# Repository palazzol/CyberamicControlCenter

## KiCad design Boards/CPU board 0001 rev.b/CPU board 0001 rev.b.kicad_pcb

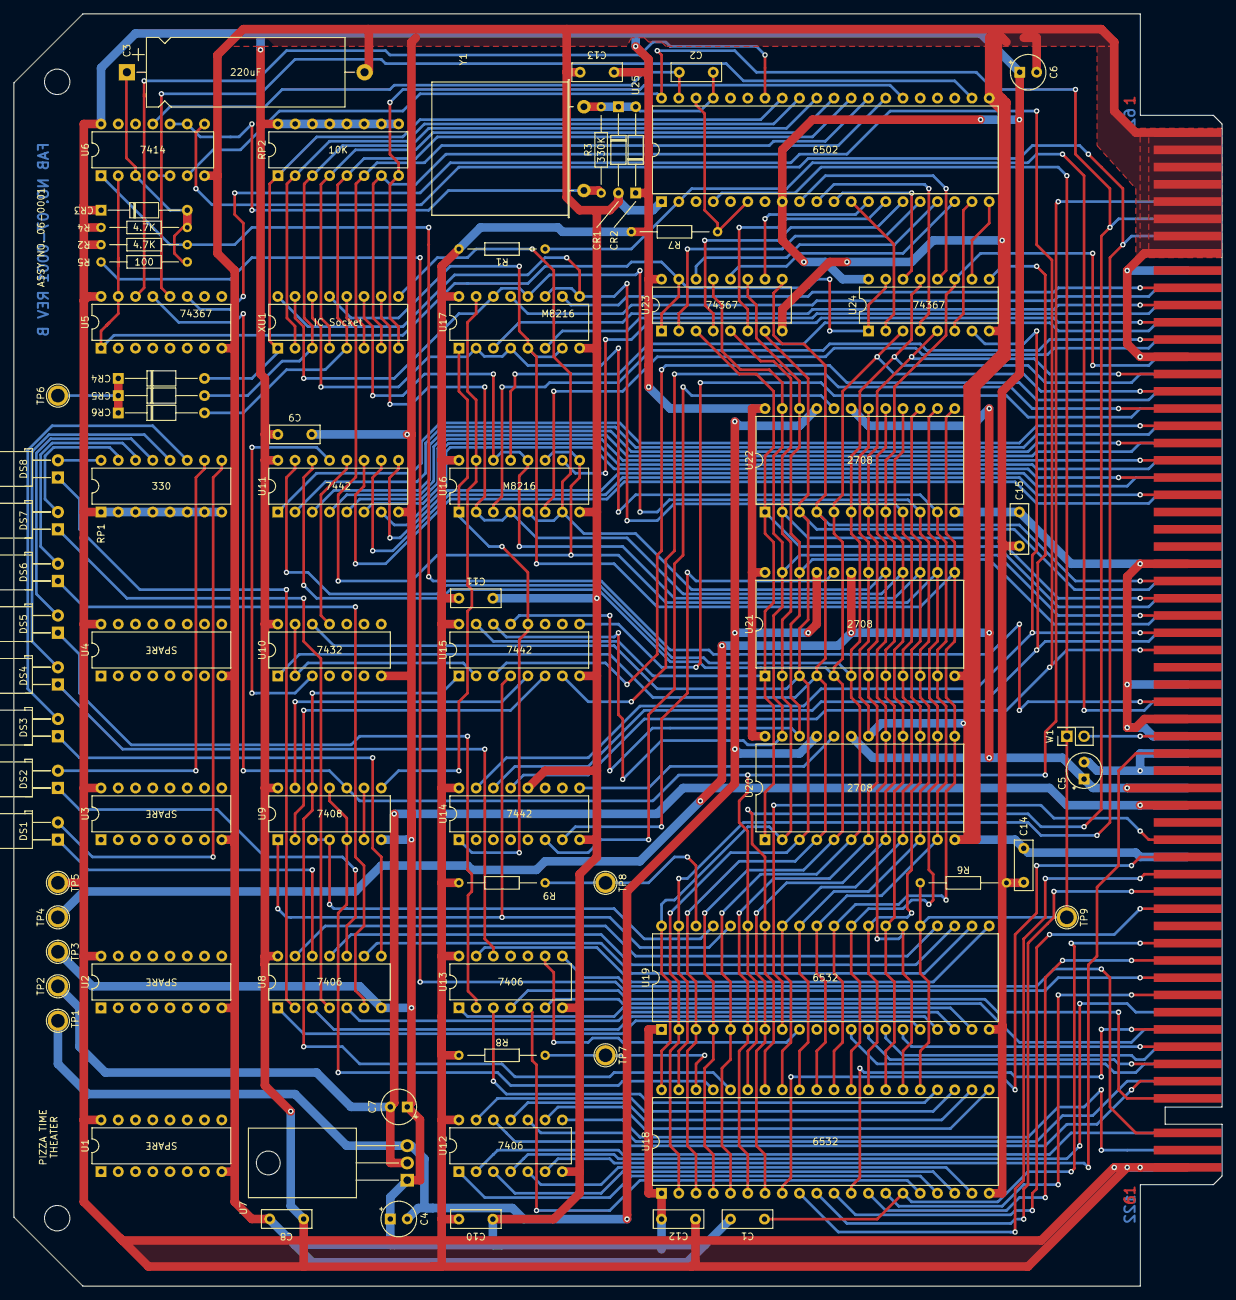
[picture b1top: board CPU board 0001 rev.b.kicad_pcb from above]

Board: 2 copper layers, 177.9 x 187.4 mm, 78 parts (0 on the bottom side), 157 nets.

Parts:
C1, C8, C9, C10, C11, C12, C13, C14, C15: 100nF; C_Rect_L7.2mm_W2.5mm_P5.00mm_FKS2_FKP2_MKS2_MKP2
C2: 10pF; C_Rect_L7.2mm_W2.5mm_P5.00mm_FKS2_FKP2_MKS2_MKP2
C3: 220uF; CP_Axial_L29.0mm_D10.0mm_P35.00mm_Horizontal
C4, C5, C6, C7: 4.7uF; CP_Radial_Tantal_D5.0mm_P2.50mm
CR1, CR2, CR3, CR4, CR5, CR6: 1N914; D_DO-35_SOD27_P12.70mm_Horizontal
DS1, DS2, DS3, DS4, DS5, DS6, DS7, DS8: LED; LED_D5.0mm_Horizontal_O3.81mm_Z15.0mm reversed
J1: CEC card edge connector large; Chuck_E_Cheese_large_card_edge
R1, R2, R4, R6, R7, R8, R9: 4.7K; R_Axial_DIN0204_L3.6mm_D1.6mm_P12.7mm_Horizontal
R3: 330K; R_Axial_DIN0204_L3.6mm_D1.6mm_P12.7mm_Horizontal
R5: 100; R_Axial_DIN0204_L3.6mm_D1.6mm_P12.7mm_Horizontal
RP1: 330; DIP-16_W7.62mm
RP2: 10K; DIP-16_W7.62mm
TP1: -5v; TestPoint_Plated_Hole_D2.0mm
TP2: -12v; TestPoint_Plated_Hole_D2.0mm
TP3: GND; TestPoint_Plated_Hole_D2.0mm
TP4: +12v; TestPoint_Plated_Hole_D2.0mm
TP5: +5v; TestPoint_Plated_Hole_D2.0mm
TP6: ~{0/2/4}; TestPoint_Plated_Hole_D2.0mm
TP7: U18 CS; TestPoint_Plated_Hole_D2.0mm
TP8: U19 CS; TestPoint_Plated_Hole_D2.0mm
TP9: IRQ; TestPoint_Plated_Hole_D2.0mm
U1, U2, U3, U4: SPARE; DIP-16_W7.62mm
U5, U23, U24: 74367; DIP-16_W7.62mm
U6: 7414; DIP-14_W7.62mm
U7: LM7905_TO220; TO-220-3_Horizontal_TabDown
U8, U12, U13: 7406; DIP-14_W7.62mm
U9: 7408; DIP-14_W7.62mm
U10: 7432; DIP-14_W7.62mm
U11, U14, U15: 7442; DIP-16_W7.62mm
U16, U17: M8216; DIP-16_W7.62mm
U18, U19: 6532; DIP-40_W15.24mm
U20, U21, U22: 2708; DIP-24_W15.24mm
U25: 6502; DIP-40_W15.24mm
W1: IRQ; PinSocket_2x01_P2.54mm_Vertical
XU1: IC Socket; DIP-16_W7.62mm
Y1: 1Mhz; Crystal_HC33-U_Horizontal

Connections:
+5V: C6.1, C8.1, C9.1, C10.1, C11.1, C12.1, C13.1, C14.1, C15.1, CR2.1 (K), CR3.1 (K), J1.61, J1.122, R1.1, R2.1, R4.1, R6.1, R7.1, R8.1, R9.1, RP1.1 (R1.1), RP1.2 (R2.1), RP1.3 (R3.1), RP1.4 (R4.1), RP1.5 (R5.1), RP1.6 (R6.1), RP1.7 (R7.1), RP1.8 (R8.1), RP2.9 (R8.2), RP2.10 (R7.2), RP2.11 (R6.2), RP2.12 (R5.2), RP2.13 (R4.2), RP2.14 (R3.2), RP2.15 (R2.2), RP2.16 (R1.2), TP5.1, U1.16 (R1.2), U2.16 (R1.2), U3.16 (R1.2), U4.16 (R1.2), U5.16 (VCC), U6.14 (VCC), U8.14 (VCC), U9.14 (VCC), U10.14 (VCC), U11.16 (VCC), U12.14 (VCC), U13.14 (VCC), U14.16 (VCC), U15.16 (VCC), U16.16 (VCC), U17.16 (VCC), U18.20 (Vcc), U19.20 (Vcc), U20.24 (VCC), U21.24 (VCC), U22.24 (VCC), U23.16 (VCC), U24.16 (VCC), U25.8 (Vcc)
+12V: C5.1, J1.39, J1.100, TP4.1, U20.19 (VDD), U21.19 (VDD), U22.19 (VDD)
-5V: C4.2, TP1.1, U7.3 (VO), U20.21 (VBB), U21.21 (VBB), U22.21 (VBB)
-12V: C7.2, J1.40, J1.101, TP2.1, U7.2 (VI)
A0: U24.12 (I5), U25.9 (A0)
A1: U24.4 (I2), U25.10 (A1)
A2: U24.14 (I6), U25.11 (A2)
A3: U24.2 (I1), U25.12 (A3)
A4: U23.10 (I4), U25.13 (A4)
A5: U23.6 (I3), U25.14 (A5)
A6: U23.4 (I2), U25.15 (A6)
A7: U23.2 (I1), U25.16 (A7)
A8: U23.14 (I6), U25.17 (A8)
A9: U23.12 (I5), U25.18 (A9)
A10: U24.6 (I3), U25.19 (A10)
A11: U24.10 (I4), U25.20 (A11)
A12: U5.12 (I5), U25.22 (A12)
AGC 1: J1.116, U19.12 (PA4)
AGC 2: J1.55, U19.13 (PA5)
AGC 4: J1.115, U19.14 (PA6)
AGC 8: J1.54, U19.15 (PA7)
AUDIO: J1.78, U15.9 (7)
B'DAY in: J1.44, U18.9 (PA1)
B'DAY out: J1.56, U12.12
BA0: J1.75, U18.7 (A0), U19.7 (A0), U20.8 (A0), U21.8 (A0), U22.8 (A0), U24.11 (O5b)
BA1: J1.15, U18.6 (A1), U19.6 (A1), U20.7 (A1), U21.7 (A1), U22.7 (A1), U24.5 (O2a)
BA2: J1.76, U11.15 (A0), U18.5 (A2), U19.5 (A2), U20.6 (A2), U21.6 (A2), U22.6 (A2), U24.13 (O6b)
BA3: J1.16, U11.14 (A1), U18.4 (A3), U19.4 (A3), U20.5 (A3), U21.5 (A3), U22.5 (A3), U24.3 (O1a)
BA4: J1.27, U10.1, U18.3 (A4), U19.3 (A4), U20.4 (A4), U21.4 (A4), U22.4 (A4), U23.9 (O4a)
BA5: J1.88, U10.12, U18.2 (A5), U19.2 (A5), U20.3 (A5), U21.3 (A5), U22.3 (A5), U23.7 (O3a)
BA6: J1.28, U18.40 (A6), U19.40 (A6), U20.2 (A6), U21.2 (A6), U22.2 (A6), U23.5 (O2a)
BA7: J1.89, U15.15 (A0), U20.1 (A7), U21.1 (A7), U22.1 (A7), U23.3 (O1a)
BA8: J1.29, U15.14 (A1), U20.23 (A8), U21.23 (A8), U22.23 (A8), U23.13 (O6b)
BA9: J1.90, U15.13 (A2), U20.22 (A9), U21.22 (A9), U22.22 (A9), U23.11 (O5b)
BA10: J1.30, U14.15 (A0), U24.7 (O3a)
BA11: J1.91, U14.14 (A1), U24.9 (O4a)
BA12: J1.31, U5.11 (O5b), U14.13 (A2)
BS1: J1.18, U11.1 (0)
BS2: J1.79, U11.2 (1)
BS3: J1.19, U11.3 (2)
BS4: J1.80, U11.4 (3)
BS5: J1.20, U11.5 (4)
BS6: J1.81, U11.6 (5)
BS7: J1.21, U11.7 (6)
BS8: J1.82, U11.9 (7)
BS9: J1.22, U11.10 (8)
BS10: J1.83, U11.11 (9)
CHEER in: J1.43, U18.8 (PA0)
CHEER out: J1.57, U13.4
D0: U17.9 (DI2), U17.11 (DO2), U18.33 (D0), U19.33 (D0), U20.9 (D0), U21.9 (D0), U22.9 (D0), XU1.16 (R1.2)
D1: U17.12 (DI3), U17.14 (DO3), U18.32 (D1), U19.32 (D1), U20.10 (D1), U21.10 (D1), U22.10 (D1), XU1.15 (R2.2)
D2: U17.2 (DO0), U17.4 (DI0), U18.31 (D2), U19.31 (D2), U20.11 (D2), U21.11 (D2), U22.11 (D2), XU1.14 (R3.2)
D3: U17.5 (DO1), U17.7 (DI1), U18.30 (D3), U19.30 (D3), U20.13 (D3), U21.13 (D3), U22.13 (D3), XU1.13 (R4.2)
D4: U16.9 (DI2), U16.11 (DO2), U18.29 (D4), U19.29 (D4), U20.14 (D4), U21.14 (D4), U22.14 (D4), XU1.12 (R5.2)
D5: U16.12 (DI3), U16.14 (DO3), U18.28 (D5), U19.28 (D5), U20.15 (D5), U21.15 (D5), U22.15 (D5), XU1.11 (R6.2)
D6: U16.2 (DO0), U16.4 (DI0), U18.27 (D6), U19.27 (D6), U20.16 (D6), U21.16 (D6), U22.16 (D6), XU1.10 (R7.2)
D7: U16.5 (DO1), U16.7 (DI1), U18.26 (D7), U19.26 (D7), U20.17 (D7), U21.17 (D7), U22.17 (D7), XU1.9 (R8.2)
DB0: J1.10, U17.10 (DB2)
DB1: J1.71, U17.13 (DB3)
DB2: J1.11, U17.3 (DB0)
DB3: J1.72, U17.6 (DB1)
DB4: J1.12, U16.10 (DB2)
DB5: J1.73, U16.13 (DB3)
DB6: J1.13, U16.3 (DB0)
DB7: J1.74, U16.6 (DB1)
DIAG in: J1.53, U18.12 (PA4)
DIAG out: J1.37, U12.6
GND: C1.2, C3.2, C4.1, C5.2, C6.2, C7.1, C8.2, C9.2, C10.2, C11.2, C12.2, C13.2, C14.2, C15.2, CR1.2 (A), J1.1, J1.2, J1.3, J1.4, J1.5, J1.6, J1.7, J1.8, J1.14, J1.26, J1.35, J1.70, J1.94, J1.97, J1.98, J1.99, J1.103, J1.104, J1.105, J1.106, J1.107, J1.108, J1.109, J1.110, J1.111, TP3.1, U1.8 (R8.1), U2.8 (R8.1), U3.8 (R8.1), U4.8 (R8.1), U5.8 (GND), U6.7 (GND), U7.1 (GND), U8.7 (GND), U9.7 (GND), U10.7 (GND), U11.8 (GND), U12.7 (GND), U13.7 (GND), U14.8 (GND), U14.12 (A3), U15.8 (GND), U16.8 (GND), U17.8 (GND), U18.1 (GND), U19.1 (GND), U20.12 (GND), U20.18 (PGM), U21.12 (GND), U21.18 (PGM), U22.12 (GND), U22.18 (PGM), U23.8 (GND), U24.8 (GND), U25.1 (VSS), U25.21 (GND)
INTRO in: J1.45, U18.10 (PA2)
INTRO out: J1.117, U12.10
MIKE SW.: J1.42, U19.8 (PA0)
NEXT in: J1.49, U18.13 (PA5)
NEXT out: J1.113, U12.4
unnamed: C2.1, CR1.1 (K), CR2.2 (A), R3.2, U25.37 (00), Y1.1
unnamed: C3.1, CR3.2 (A), R4.2, R5.2, U6.3
unnamed: CR4.2 (A), RP2.1 (R1.1), U25.33 (D0), XU1.1 (R1.1)
unnamed: CR4.1 (K), CR5.1 (K), CR6.1 (K), TP6.1
unnamed: CR5.2 (A), RP2.3 (R3.1), U25.31 (D2), XU1.3 (R3.1)
unnamed: CR6.2 (A), RP2.5 (R5.1), U25.29 (D4), XU1.5 (R5.1)
unnamed: DS1.2 (A), RP1.9 (R8.2)
unnamed: DS1.1 (K), U8.12
unnamed: DS2.2 (A), RP1.10 (R7.2)
unnamed: DS2.1 (K), U8.10
unnamed: DS3.2 (A), RP1.11 (R6.2)
unnamed: DS3.1 (K), U8.8
unnamed: DS4.2 (A), RP1.12 (R5.2)
unnamed: DS4.1 (K), U13.12
unnamed: DS5.2 (A), RP1.13 (R4.2)
unnamed: DS5.1 (K), U13.2
unnamed: DS6.2 (A), RP1.14 (R3.2)
unnamed: DS6.1 (K), U8.6
unnamed: DS7.2 (A), RP1.15 (R2.2)
unnamed: DS7.1 (K), U8.4
unnamed: DS8.2 (A), RP1.16 (R1.2)
unnamed: DS8.1 (K), U8.2
unnamed: R3.1, U6.9, U6.10, Y1.2
unnamed: RP2.2 (R2.1), U25.32 (D1), XU1.2 (R2.1)
unnamed: RP2.4 (R4.1), U25.30 (D3), XU1.4 (R4.1)
unnamed: RP2.6 (R6.1), U25.28 (D5), XU1.6 (R6.1)
unnamed: RP2.7 (R7.1), U25.27 (D6), XU1.7 (R7.1)
unnamed: RP2.8 (R8.1), U25.26 (D7), XU1.8 (R8.1)
unnamed: U6.4, U6.5
unnamed: U9.6, U9.9
unnamed: U10.3, U11.13 (A2)
unnamed: U10.11, U11.12 (A3)
unnamed: U14.1 (0), U15.12 (A3), U16.1 (~CS), U17.1 (~CS)
unnamed: U9.8, U16.15 (IN/~OUT), U17.15 (IN/~OUT)
unnamed: R8.2, TP7.1, U18.38 (CS1)
unnamed: U13.3, U18.24 (PB0)
unnamed: U12.13, U18.23 (PB1)
unnamed: U12.11, U18.22 (PB2)
unnamed: U12.9, U18.21 (PB3)
unnamed: U12.5, U18.19 (PB4)
unnamed: U12.3, U18.18 (PB5)
unnamed: U12.1, U18.17 (PB6)
unnamed: U13.5, U18.16 (PB7)
unnamed: U9.5, U9.11, U18.37 (~CS2)
unnamed: R9.2, TP8.1, U19.38 (CS1)
unnamed: U13.9, U19.9 (PA1)
unnamed: U8.13, U19.24 (PB0)
unnamed: U8.11, U19.23 (PB1)
unnamed: U8.9, U19.22 (PB2)
unnamed: U13.13, U19.21 (PB3)
unnamed: U13.1, U19.19 (PB4)
unnamed: U8.5, U19.18 (PB5)
unnamed: U8.3, U19.17 (PB6)
unnamed: U8.1, U19.16 (PB7)
unnamed: U9.3, U9.4, U19.37 (~CS2)
unnamed: U5.1 (OEa), U5.15 (OEb), U6.2, U23.1 (OEa), U23.15 (OEb), U24.1 (OEa), U24.15 (OEb)
unnamed: C2.2, U6.11, U25.39 (02)
unnamed: R7.2, U25.6 (~NMI), U25.38 (SO)
PHI2: J1.68, U6.8, U18.39 (02), U19.39 (02)
PROG in: C1.1, J1.48, U18.15 (PA7)
PROG out: J1.114, U13.6
RDY: J1.95, R1.2, U25.2 (RDY)
RESET out: J1.59, U13.8
R/~W: J1.66, U5.13 (O6b), U9.10, U18.35 (R/~W), U19.35 (R/~W)
SKIP in: J1.51, U18.14 (PA6)
SKIP out: J1.120, U12.2
SPEC in: J1.46, U18.11 (PA3)
SPEC out: J1.121, U12.8
UART: J1.77, U15.3 (2)
XPRT: J1.17, U15.7 (6)
cpu R/~W: U5.14 (I6), U25.34 (R/~W)
/CARDS: U10.2, U10.13, U15.2 (1)
/CS U20: U14.9 (7), U20.20 (~CS)
/CS U21: U14.7 (6), U21.20 (~CS)
/CS U22: U14.6 (5), U22.20 (~CS)
/HOLD in: J1.34, R2.2, U6.1
/IRQ: R6.2, TP9.1, U18.25 (~IRQ), U19.25 (~IRQ), U25.4 (~IRQ), W1.1
/IRQ out: J1.36, W1.2
/RAM: U9.12, U15.1 (0), U18.36 (/RS)
/RESET: J1.67, U6.6, U18.34 (~RESET), U19.34 (~RESET), U25.40 (~RESET)
/RESET in: J1.50, R5.1
/STACK: U9.1, U15.4 (3), U19.36 (/RS)
/U18: U9.13, U15.5 (4)
/U19: U9.2, U15.6 (5)

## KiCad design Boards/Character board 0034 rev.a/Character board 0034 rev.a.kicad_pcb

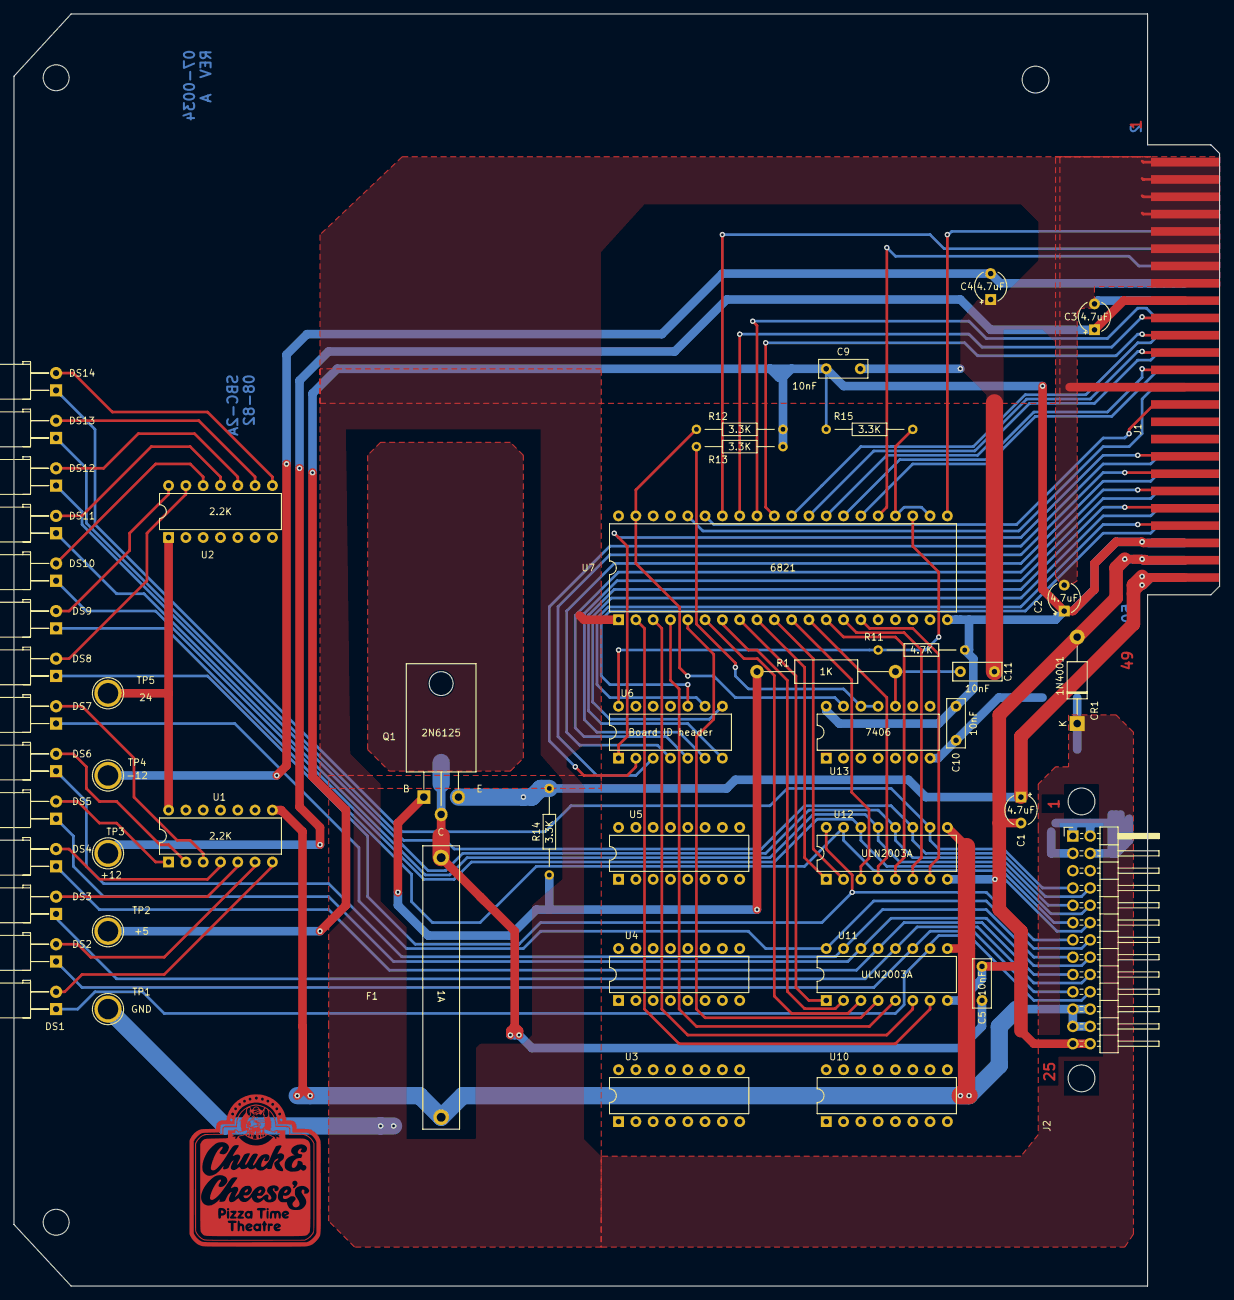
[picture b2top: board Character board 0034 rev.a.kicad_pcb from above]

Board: 2 copper layers, 176.9 x 186.7 mm, 49 parts (0 on the bottom side), 79 nets.

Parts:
C1, C2, C3, C4: 4.7uF; CP_Radial_Tantal_D4mm_P3.81mm
C5, C9, C10, C11: 10nF; C_Rect_L7.0mm_W2.5mm_P5.00mm
CR1: 1N4001; D_DO-41_SOD81_P12.70mm_Horizontal
DS1, DS2, DS3, DS4, DS5, DS6, DS7, DS8, DS9, DS10, DS11, DS12, DS13, DS14: LED; LED_D5.0mm_Horizontal_O3.81mm_Z15.0mm reversed
F1: 1A; Fuseholder_Littelfuse_445_030_series_5x30mm
J1: card edge; Chuck_E_Cheese_small_card_edge
J2: character connector; PinHeader_2x13_P2.54mm_Horizontal
Q1: 2N6125; TO-220-3_Horizontal_TabDown
R1: 1K; R_Axial_DIN0309_L9.0mm_D3.2mm_P20.32mm_Horizontal
R11: 4.7K; R_Axial_DIN0204_L3.6mm_D1.6mm_P12.7mm_Horizontal
R12, R13, R14, R15: 3.3K; R_Axial_DIN0204_L3.6mm_D1.6mm_P12.7mm_Horizontal
TP1: GND; TestPoint_Plated_Hole_D3.0mm
TP2: +5; TestPoint_Plated_Hole_D3.0mm
TP3: +12; TestPoint_Plated_Hole_D3.0mm
TP4: -12; TestPoint_Plated_Hole_D3.0mm
TP5: 24; TestPoint_Plated_Hole_D3.0mm
U1, U2: 2.2K; DIP-14_W7.62mm
U3, U4, U5, U10: Unused DIP; DIP-16_W7.62mm
U6: Board ID header; DIP-14_W7.62mm
U7: 6821; DIP-40_W15.24mm
U11, U12: ULN2003A; DIP-16_W7.62mm
U13: 7406; DIP-14_W7.62mm

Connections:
5V: C2.1, C9.1, C10.1, J1.45, J1.46, R11.1, R12.2, R13.2, R15.1, TP2.1, U7.20 (VCC), U13.14 (VCC)
12V: C3.1, J1.17, TP3.1
24R: C1.2, C5.1, CR1.2 (A), J1.47, J1.48, J2.25, J2.26, U11.8 (GND), U12.8 (GND)
24V: C1.1, J1.49, J1.50, Q1.3 (E), R14.2
24Vout: F1.2, J2.21, J2.22, J2.23, J2.24, TP5.1, U1.8 (R7.2), U1.9 (R6.2), U1.10 (R5.2), U1.11 (R4.2), U1.12 (R3.2), U1.13 (R2.2), U1.14 (R1.2), U2.1 (R1.1), U2.2 (R2.1), U2.3 (R3.1), U2.4 (R4.1), U2.5 (R5.1), U2.6 (R6.1), U2.7 (R7.1), U11.9 (COM), U12.9 (COM)
-12V: C4.2, J1.16, TP4.1
A0out: DS1.1 (K), J2.20, U11.10 (O7)
A1out: DS2.1 (K), J2.19, U11.11 (O6)
A2out: DS3.1 (K), J2.18, U11.12 (O5)
A3out: DS4.1 (K), J2.17, U11.13 (O4)
A4out: DS5.1 (K), J2.16, U11.14 (O3)
A5out: DS6.1 (K), J2.15, U11.15 (O2)
A6out: DS7.1 (K), J2.14, U11.16 (O1)
A7out: DS8.1 (K), J2.13, U12.16 (O1)
B0out: DS9.1 (K), J2.12, U12.15 (O2)
B1out: DS10.1 (K), J2.11, U12.14 (O3)
B2out: DS11.1 (K), J2.10, U12.13 (O4)
B3out: DS12.1 (K), J2.9, U12.12 (O5)
B4out: DS13.1 (K), J2.8, U12.11 (O6)
B5out: DS14.1 (K), J2.7, U12.10 (O7)
BA0: J1.28, U7.36 (RS0)
BA1: J1.29, U7.35 (RS1)
BS1: J1.35, U6.1
BS2: J1.36, U6.2
BS3: J1.37, U6.3
BS4: J1.38, U6.4
BS5: J1.39, U6.5
BS6: J1.40, U6.6
BS7: J1.41, U6.7
BS8: J1.42, U6.8
BS9: J1.43, U6.9
BS10: J1.44, U6.10
DBB0: J1.19, U7.33 (D0)
DBB1: J1.20, U7.32 (D1)
DBB2: J1.21, U7.31 (D2)
DBB3: J1.22, U7.30 (D3)
DBB4: J1.23, U7.29 (D4)
DBB5: J1.24, U7.28 (D5)
DBB6: J1.25, U7.27 (D6)
DBB7: J1.26, U7.26 (D7)
GND: C2.2, C3.2, C4.1, C9.2, C10.2, C11.2, CR1.1 (K), J1.1, J1.3, J1.5, J1.7, J1.9, J1.11, J1.13, J1.15, J1.18, J1.27, J2.1, J2.2, J2.3, J2.4, TP1.1, U7.1 (VSS), U13.7 (GND)
unnamed: C11.1, R1.2, U13.10
unnamed: DS1.2 (A), U1.7 (R7.1)
unnamed: DS2.2 (A), U1.6 (R6.1)
unnamed: DS3.2 (A), U1.5 (R5.1)
unnamed: DS4.2 (A), U1.4 (R4.1)
unnamed: DS5.2 (A), U1.1 (R1.1)
unnamed: DS6.2 (A), U1.2 (R2.1)
unnamed: DS7.2 (A), U1.3 (R3.1)
unnamed: DS8.2 (A), U2.13 (R2.2)
unnamed: DS9.2 (A), U2.14 (R1.2)
unnamed: DS10.2 (A), U2.12 (R3.2)
unnamed: DS11.2 (A), U2.11 (R4.2)
unnamed: DS12.2 (A), U2.10 (R5.2)
unnamed: DS13.2 (A), U2.9 (R6.2)
unnamed: DS14.2 (A), U2.8 (R7.2)
unnamed: Q1.1 (B), R1.1, R14.1
unnamed: C5.2, F1.1, Q1.2 (C)
unnamed: R13.1, U13.11, U13.12
unnamed: R11.2, U6.14, U7.23 (~CS2)
unnamed: R12.1, U7.39 (CA2), U13.13
unnamed: R15.2, U7.22 (CS0), U7.24 (CS1)
PA0: U7.2 (PA0), U11.7 (I7)
PA1: U7.3 (PA1), U11.6 (I6)
PA2: U7.4 (PA2), U11.5 (I5)
PA3: U7.5 (PA3), U11.4 (I4)
PA4: U7.6 (PA4), U11.3 (I3)
PA5: U7.7 (PA5), U11.2 (I2)
PA6: U7.8 (PA6), U11.1 (I1)
PA7: U7.9 (PA7), U12.1 (I1)
PB0: U7.10 (PB0), U12.2 (I2)
PB1: U7.11 (PB1), U12.3 (I3)
PB2: U7.12 (PB2), U12.4 (I4)
PB3: U7.13 (PB3), U12.5 (I5)
PB4: U7.14 (PB4), U12.6 (I6)
PB5: U7.15 (PB5), U12.7 (I7)
PHI2: J1.14, U7.25 (ENABLE)
R/~W: J1.10, U7.21 (R/~W)
~MRST: J1.12, U7.34 (~RESET)

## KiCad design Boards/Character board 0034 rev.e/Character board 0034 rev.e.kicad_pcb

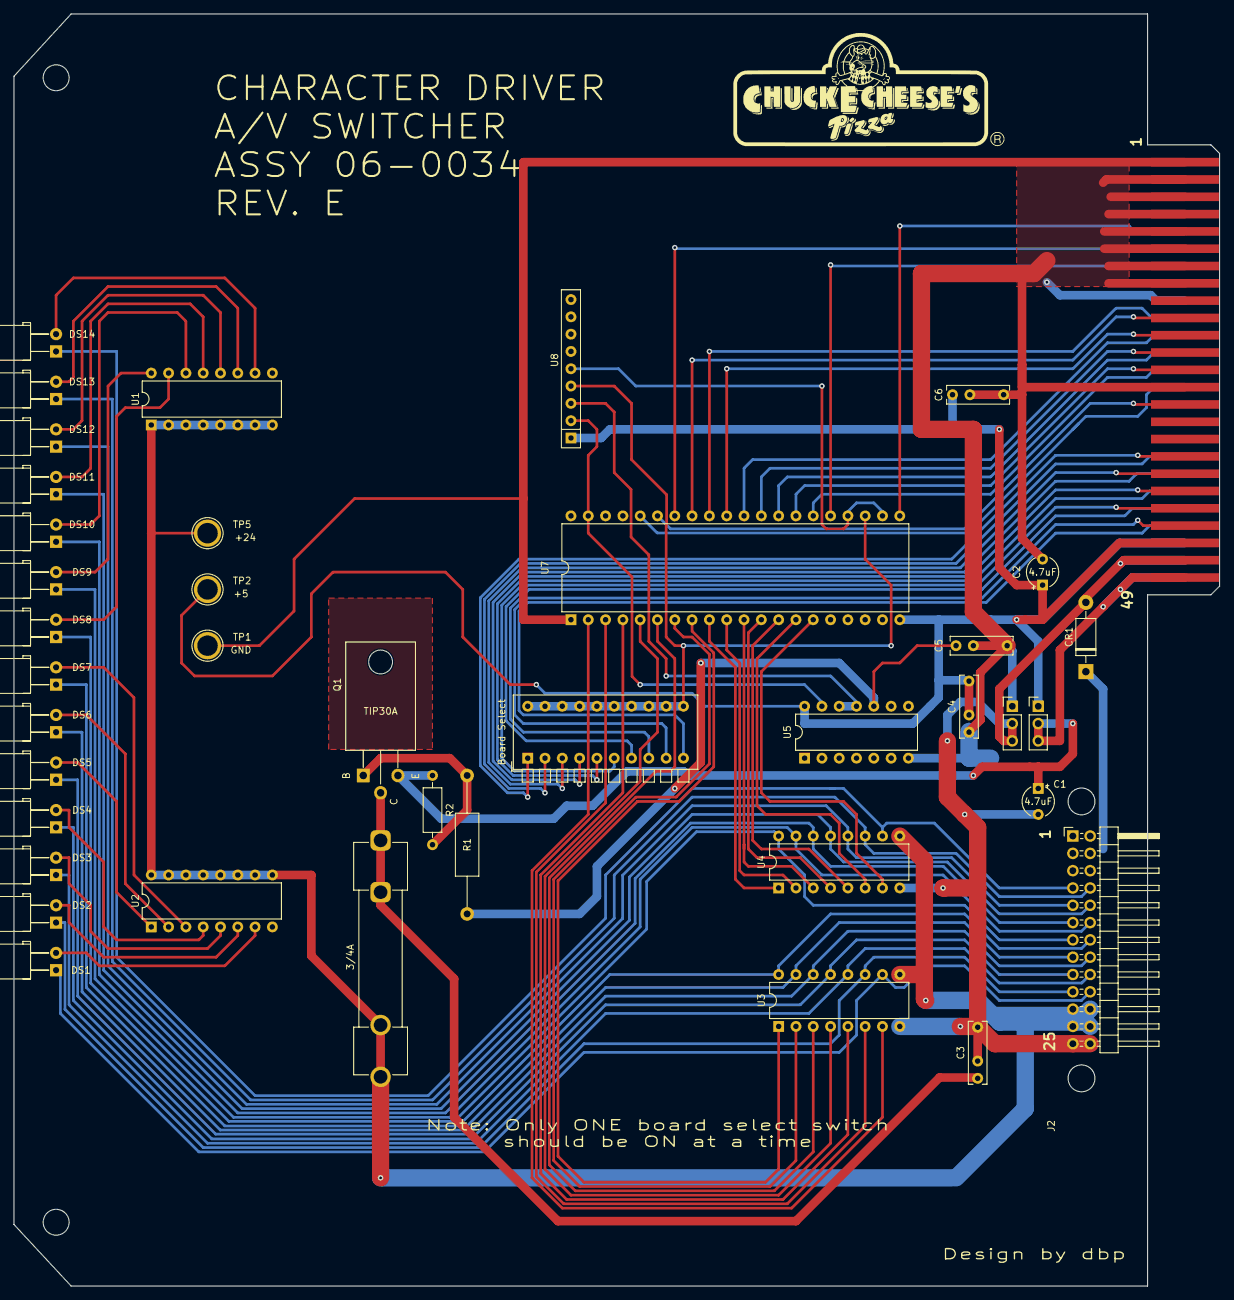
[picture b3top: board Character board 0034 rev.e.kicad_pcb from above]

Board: 2 copper layers, 176.9 x 186.7 mm, 40 parts (0 on the bottom side), 77 nets.

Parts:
C1, C2: 4.7uF; CP_Radial_Tantal_D4mm_P3.81mm
C3, C4, C5, C6: 100nF; C_Rect_L9.0mm_W2.5mm_P7.50mm_MKT dual
CR1: 1N4001; D_DO-41_SOD81_P10.16mm_Horizontal
DS1, DS2, DS3, DS4, DS5, DS6, DS7, DS8, DS9, DS10, DS11, DS12, DS13, DS14: LED; LED_D5.0mm_Horizontal_O3.81mm_Z15.0mm reversed
F1: 3/4A; Fuseholder_Clip-6.3x32mm_Littelfuse_102071_Inline_P34.70x7.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
J1: card edge; Chuck_E_Cheese_small_card_edge
J2: character connector; PinHeader_2x13_P2.54mm_Horizontal
J3: power jumper; PinHeader_1x03_P2.54mm_Vertical
J4: return jumper; PinHeader_1x03_P2.54mm_Vertical
Q1: TIP30A; TO-220-3_Horizontal_TabDown
R1: 1K; R_Axial_DIN0309_L9.0mm_D3.2mm_P20.32mm_Horizontal
R2: 3.3K; R_Axial_DIN0207_L6.3mm_D2.5mm_P10.16mm_Horizontal
TP1: GND; TestPoint_Plated_Hole_D3.0mm
TP2: +5; TestPoint_Plated_Hole_D3.0mm
TP5: +24; TestPoint_Plated_Hole_D3.0mm
U1, U2: 2.2K; DIP-16_W7.62mm
U3, U4: ULN2003A; DIP-16_W7.62mm
U5: 7406; DIP-14_W7.62mm
U6: Board Select; SW_DIP_SPSTx10_Piano_10.8x26.96mm_W7.62mm_P2.54mm
U7: 6821; DIP-40_W15.24mm
U8: 4.7K; R_Array_SIP9

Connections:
5V: C2.1, C4.2, C6.1, J1.45, J1.46, J3.1, TP2.1, U5.14 (VCC), U7.20 (VCC), U8.1 (common)
5vpu1: U5.13, U7.39 (CA2), U8.2 (R1)
5vpu2: U5.11, U5.12, U8.3 (R2)
5vpu3: U6.11, U6.12, U6.13, U6.14, U6.15, U6.16, U6.17, U6.18, U6.19, U6.20, U7.23 (~CS2), U8.4 (R3)
5vpu4: U7.22 (CS0), U7.24 (CS1), U8.5 (R4)
24R: C1.2, C3.2, CR1.2 (A), J1.47, J1.48, J2.25, J2.26, J4.2, J4.3, U3.8 (GND), U4.8 (GND)
24V: C1.1, J1.49, J1.50, J3.2, J3.3, Q1.3 (E), R2.2
24Vout: F1.2, J2.21, J2.22, J2.23, J2.24, TP5.1, U1.1 (R1.1), U1.2 (R2.1), U1.3 (R3.1), U1.4 (R4.1), U1.5 (R5.1), U1.6 (R6.1), U1.7 (R7.1), U1.8 (R8.1), U2.9 (R8.2), U2.10 (R7.2), U2.11 (R6.2), U2.12 (R5.2), U2.13 (R4.2), U2.14 (R3.2), U2.15 (R2.2), U2.16 (R1.2), U3.9 (COM), U4.9 (COM)
A0out: DS1.1 (K), J2.20, U3.10 (O7)
A1out: DS2.1 (K), J2.19, U3.11 (O6)
A2out: DS3.1 (K), J2.18, U3.12 (O5)
A3out: DS4.1 (K), J2.17, U3.13 (O4)
A4out: DS5.1 (K), J2.16, U3.14 (O3)
A5out: DS6.1 (K), J2.15, U3.15 (O2)
A6out: DS7.1 (K), J2.14, U3.16 (O1)
A7out: DS8.1 (K), J2.13, U4.16 (O1)
B0out: DS9.1 (K), J2.12, U4.15 (O2)
B1out: DS10.1 (K), J2.11, U4.14 (O3)
B2out: DS11.1 (K), J2.10, U4.13 (O4)
B3out: DS12.1 (K), J2.9, U4.12 (O5)
B4out: DS13.1 (K), J2.8, U4.11 (O6)
B5out: DS14.1 (K), J2.7, U4.10 (O7)
BA0: J1.28, U7.36 (RS0)
BA1: J1.29, U7.35 (RS1)
BS1: J1.35, U6.1
BS2: J1.36, U6.2
BS3: J1.37, U6.3
BS4: J1.38, U6.4
BS5: J1.39, U6.5
BS6: J1.40, U6.6
BS7: J1.41, U6.7
BS8: J1.42, U6.8
BS9: J1.43, U6.9
BS10: J1.44, U6.10
DBB0: J1.19, U7.33 (D0)
DBB1: J1.20, U7.32 (D1)
DBB2: J1.21, U7.31 (D2)
DBB3: J1.22, U7.30 (D3)
DBB4: J1.23, U7.29 (D4)
DBB5: J1.24, U7.28 (D5)
DBB6: J1.25, U7.27 (D6)
DBB7: J1.26, U7.26 (D7)
GND: C2.2, C4.1, C5.2, C6.2, CR1.1 (K), J1.1, J1.3, J1.5, J1.7, J1.9, J1.11, J1.13, J1.15, J1.18, J1.27, J2.1, J2.2, J2.3, J2.4, J4.1, TP1.1, U5.7 (GND), U7.1 (VSS)
unnamed: C5.1, R1.2, U5.10
unnamed: DS1.2 (A), U2.7 (R7.1)
unnamed: DS2.2 (A), U2.6 (R6.1)
unnamed: DS3.2 (A), U2.5 (R5.1)
unnamed: DS4.2 (A), U2.4 (R4.1)
unnamed: DS5.2 (A), U2.1 (R1.1)
unnamed: DS6.2 (A), U2.2 (R2.1)
unnamed: DS7.2 (A), U2.3 (R3.1)
unnamed: DS8.2 (A), U1.15 (R2.2)
unnamed: DS9.2 (A), U1.16 (R1.2)
unnamed: DS10.2 (A), U1.14 (R3.2)
unnamed: DS11.2 (A), U1.13 (R4.2)
unnamed: DS12.2 (A), U1.12 (R5.2)
unnamed: DS13.2 (A), U1.11 (R6.2)
unnamed: DS14.2 (A), U1.10 (R7.2)
unnamed: Q1.1 (B), R1.1, R2.1
unnamed: C3.1, F1.1, Q1.2 (C)
PA0: U3.7 (I7), U7.2 (PA0)
PA1: U3.6 (I6), U7.3 (PA1)
PA2: U3.5 (I5), U7.4 (PA2)
PA3: U3.4 (I4), U7.5 (PA3)
PA4: U3.3 (I3), U7.6 (PA4)
PA5: U3.2 (I2), U7.7 (PA5)
PA6: U3.1 (I1), U7.8 (PA6)
PA7: U4.1 (I1), U7.9 (PA7)
PB0: U4.2 (I2), U7.10 (PB0)
PB1: U4.3 (I3), U7.11 (PB1)
PB2: U4.4 (I4), U7.12 (PB2)
PB3: U4.5 (I5), U7.13 (PB3)
PB4: U4.6 (I6), U7.14 (PB4)
PB5: U4.7 (I7), U7.15 (PB5)
PHI2: J1.14, U7.25 (ENABLE)
R/~W: J1.10, U7.21 (R/~W)
~MRST: J1.12, U7.34 (~RESET)
